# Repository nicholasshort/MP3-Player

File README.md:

# MP3 Player

This is a simple MP3 player designed to be small, lightweight, and long-lasting. The goal is something I can bring on runs, hikes, or long trips that provides 24+ hours of music on a single charge with wired headphones. Firmware is currently in the works, with low level hardware drivers completed.

## Block diagram

## Hardware

- **MCU**: STM32F411CEU6 (Cortex-M4F @ 100 MHz, USB OTG FS)
- **DAC**: TI TAD5242 stereo DAC over I²S, 3.5 mm headphone jack
- **Storage**: microSD card (SPI)
- **Power**: USB-C input, TI BQ24259 Li-ion charger, dual TPS7A20 LDOs for analog/digital rails
- **Controls**: 4 tactile switches (PWR, MENU, PLAY, NEXT), 2 × WS2812B-2020 RGB LEDs
- **PCB**: 4-layer, 50 × 50 mm, KiCad

## Repository layout

- `MP3-Player-PCB/` — KiCad project (schematics, board, libraries)
- `MP3-Player-PCB/Manufacturing/` — Gerbers, BOM, and pick-and-place files for JLCPCB
- `MP3-Player-Firmware/` — STM32CubeIDE project
- `images/` — Photos of the board

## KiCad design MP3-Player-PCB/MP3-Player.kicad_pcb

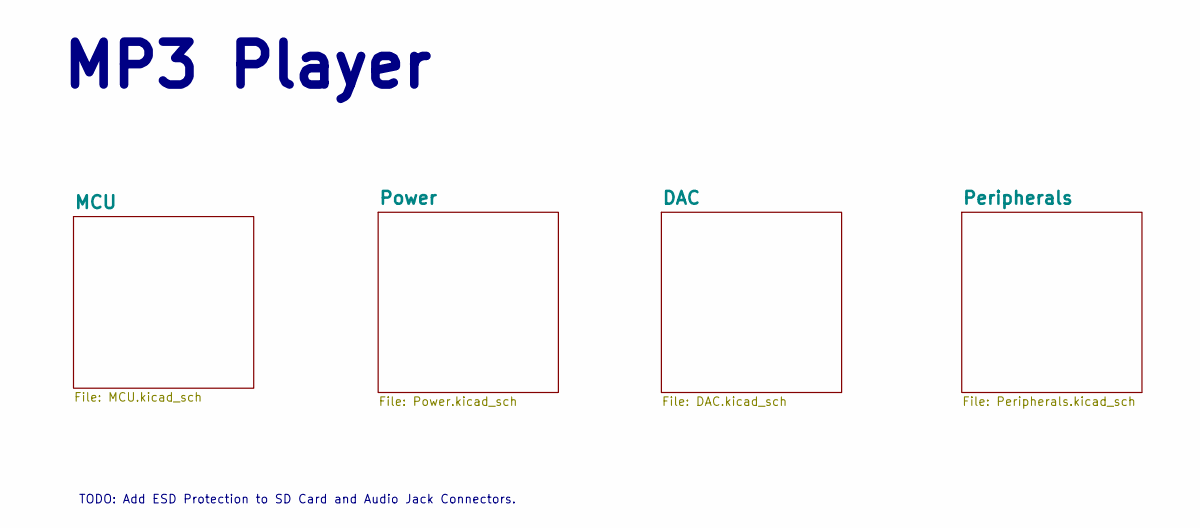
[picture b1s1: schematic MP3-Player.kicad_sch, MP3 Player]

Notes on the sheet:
MP3 Player
TODO: Add ESD Protection to SD Card and Audio Jack Connectors.

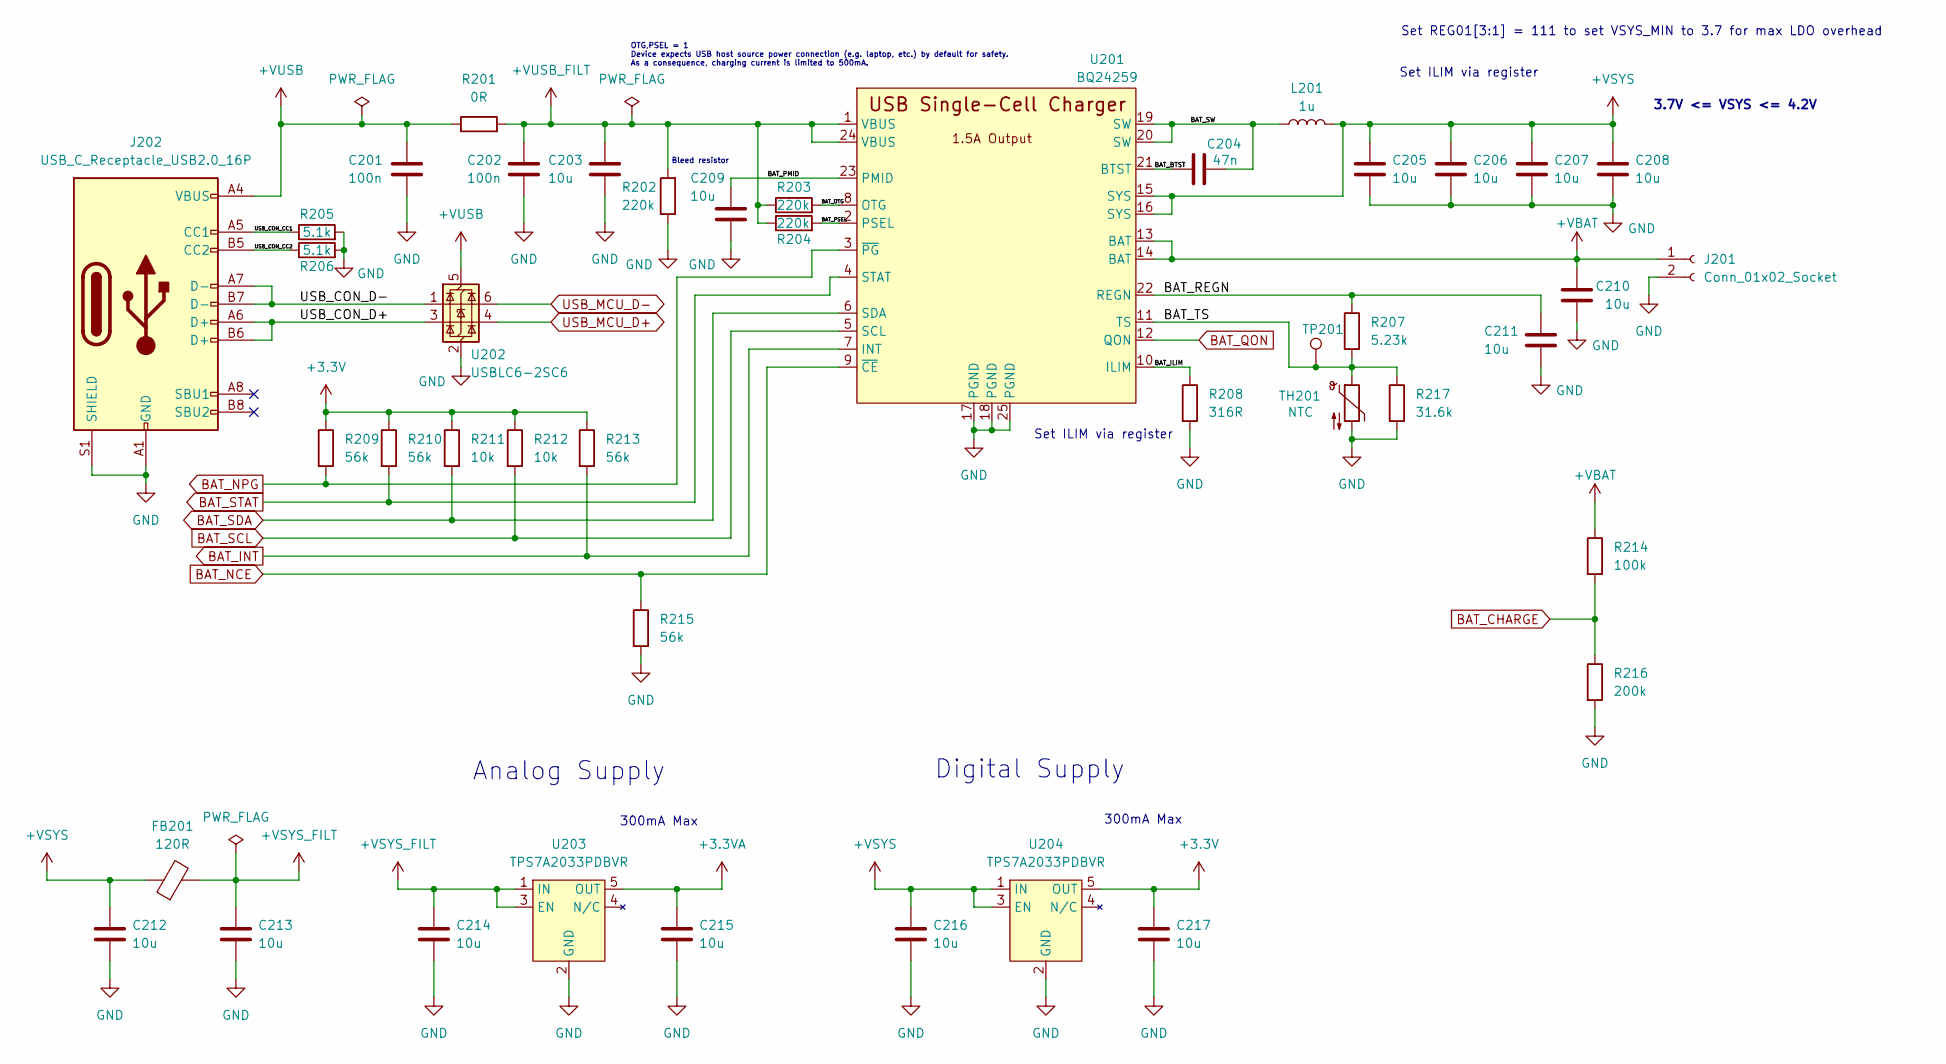
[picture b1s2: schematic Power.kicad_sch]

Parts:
C201, C202: 100n; C_0402_1005Metric; JLCPCB Part # C1525
C203, C209, C211, C212, C213: 10u; C_0603_1608Metric; JLCPCB Part # C19702
C204: 47n; C_0402_1005Metric; JLCPCB Part # C82219
C205, C206, C207, C208, C210, C214, C215, C216, C217: 10u; C_0805_2012Metric; JLCPCB Part # C15850
FB201: 120R; L_0805_2012Metric; JLCPCB Part # C5671
J201: Conn_01x02_Socket; Molex_PicoBlade_53048-0210_1x02_P1.25mm_Horizontal; JLCPCB Part # C505099
J202: USB_C_Receptacle_USB2.0_16P; USB_C_Receptacle_HRO_TYPE-C-31-M-12; JLCPCB Part # C165948
L201: 1u; L_Sunlord_SWPA3015S; JLCPCB Part # C43388
R201: 0R; R_0603_1608Metric; JLCPCB Part # C15402
R202, R203, R204: 220k; R_0402_1005Metric; JLCPCB Part # C25546
R205, R206: 5.1k; R_0402_1005Metric; JLCPCB Part # C25905
R207: 5.23k; R_0402_1005Metric; JLCPCB Part # C25907
R208: 316R; R_0402_1005Metric; JLCPCB Part # C247119
R209, R210, R213, R215: 56k; R_0402_1005Metric; JLCPCB Part # C25796
R211, R212: 10k; R_0402_1005Metric; JLCPCB Part # C25744
R214: 100k; R_0402_1005Metric; JLCPCB Part # C25741
R216: 200k; R_0402_1005Metric; JLCPCB Part # C25764
R217: 31.6k; R_0402_1005Metric; JLCPCB Part # C11463
TH201: NTC; R_0603_1608Metric; JLCPCB Part # C700814
TP201: TestPoint; TestPoint_Pad_1.0x1.0mm
U201: BQ24259; VQFN-24-1EP_4x4mm_P0.5mm_EP2.5x2.5mm; JLCPCB Part # C473366
U202: USBLC6-2SC6; SOT-23-6; JLCPCB Part # C7519
U203, U204: TPS7A2033PDBVR; SOT-23-5; JLCPCB Part # C2862740

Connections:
+3.3V: C217.1, R209.1, R210.1, R211.1, R212.1, R213.1, U204.5 (OUT); also elsewhere on the board
+3.3VA: C215.1, U203.5 (OUT); also elsewhere on the board
+VBAT: C210.1, J201.1, R214.1, U201.13 (BAT), U201.14 (BAT); also elsewhere on the board
+VSYS: C205.1, C206.1, C207.1, C208.1, C212.1, C216.1, FB201.1, L201.2, U201.15 (SYS), U201.16 (SYS), U204.1 (IN), U204.3 (EN); also elsewhere on the board
+VSYS_FILT: C213.1, C214.1, FB201.2, U203.1 (IN), U203.3 (EN)
+VUSB: C201.1, J202.A4 (VBUS), J202.A9 (VBUS), J202.B4 (VBUS), J202.B9 (VBUS), R201.1, U202.5 (VBUS)
+VUSB_FILT: C202.1, C203.1, R201.2, R202.2, R203.1, R204.1, U201.1 (VBUS), U201.24 (VBUS)
/Power/BAT_BTST: C204.1, U201.21 (BTST)
/Power/BAT_ILIM: R208.1, U201.10 (ILIM)
/Power/BAT_OTG: R203.2, U201.8 (OTG)
/Power/BAT_PMID: C209.1, U201.23 (PMID)
/Power/BAT_PSEL: R204.2, U201.2 (PSEL)
/Power/BAT_REGN: C211.1, R207.1, U201.22 (REGN)
/Power/BAT_SW: C204.2, L201.1, U201.19 (SW), U201.20 (SW)
/Power/BAT_TS: R207.2, R217.1, TH201.1, TP201.1, U201.11 (TS)
/Power/USB_CON_CC1: J202.A5 (CC1), R205.1
/Power/USB_CON_CC2: J202.B5 (CC2), R206.1
/Power/USB_CON_D+: J202.A6 (D+), J202.B6 (D+), U202.3 (I/O2)
/Power/USB_CON_D-: J202.A7 (D-), J202.B7 (D-), U202.1 (I/O1)
BAT_CHARGE: R214.2, R216.1; also elsewhere on the board
BAT_INT: R213.2, U201.7 (INT); also elsewhere on the board
BAT_NCE: R215.1, U201.9 (~CE); also elsewhere on the board
BAT_NPG: R209.2, U201.3 (~PG); also elsewhere on the board
BAT_QON: U201.12 (QON); also elsewhere on the board
BAT_SCL: R212.2, U201.5 (SCL); also elsewhere on the board
BAT_SDA: R211.2, U201.6 (SDA); also elsewhere on the board
BAT_STAT: R210.2, U201.4 (STAT); also elsewhere on the board
GND: C201.2, C202.2, C203.2, C205.2, C206.2, C207.2, C208.2, C209.2, C210.2, C211.2, C212.2, C213.2, C214.2, C215.2, C216.2, C217.2, J201.2, J202.A1 (GND), J202.A12 (GND), J202.B1 (GND), J202.B12 (GND), J202.S1 (SHIELD), R202.1, R205.2, R206.2, R208.2, R215.2, R216.2, R217.2, TH201.2, U201.17 (PGND), U201.18 (PGND), U201.25 (PGND), U202.2 (GND), U203.2 (GND), U204.2 (GND); also elsewhere on the board
USB_MCU_D+: U202.4 (I/O2); also elsewhere on the board
USB_MCU_D-: U202.6 (I/O1); also elsewhere on the board

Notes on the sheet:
Analog Supply
Set ILIM via register
Bleed resistor
300mA Max
Digital Supply
OTG,PSEL = 1 Device expects USB host source power connection (e.g. laptop, etc.) by default for safety. As a consequence, charging current is limited to 500mA.
3.7V <= VSYS <= 4.2V
Set REG01[3:1] = 111 to set VSYS_MIN to 3.7 for max LDO overhead

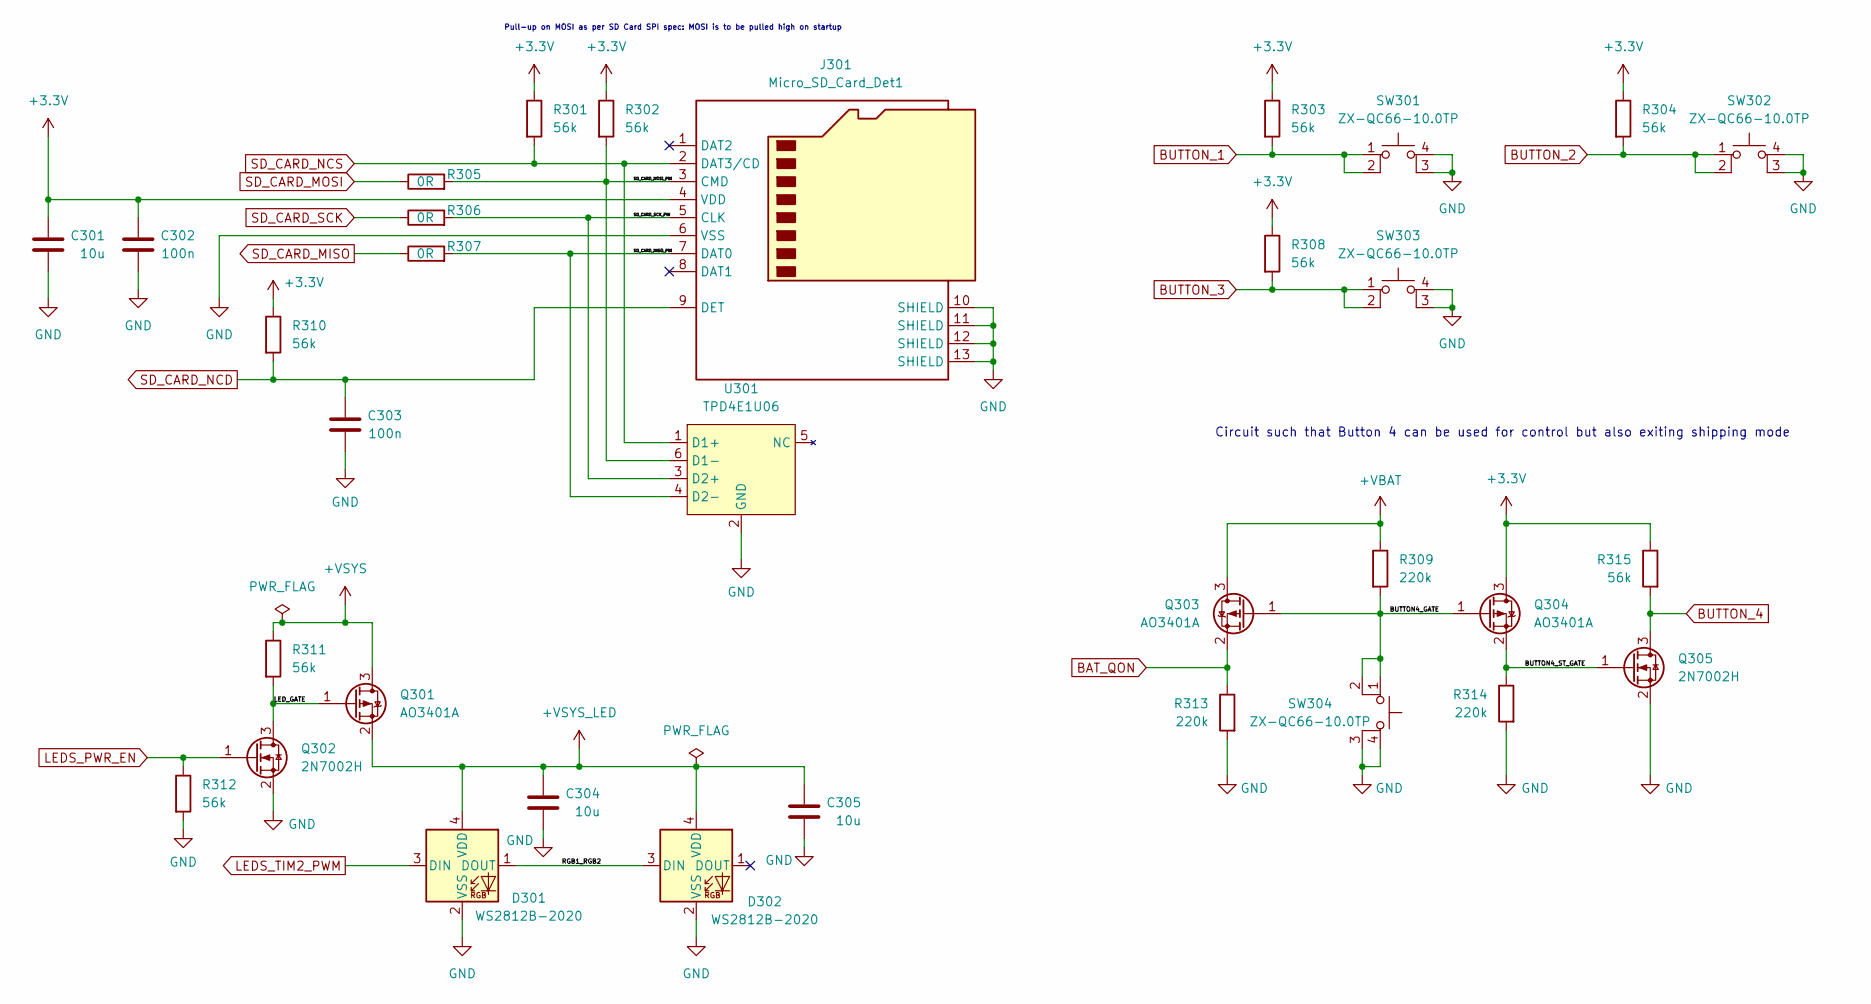
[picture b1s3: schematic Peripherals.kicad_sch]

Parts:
C301, C304, C305: 10u; C_0603_1608Metric; JLCPCB Part # C19702
C302, C303: 100n; C_0402_1005Metric; JLCPCB Part # C1525
D301, D302: WS2812B-2020; LED_WS2812B-2020_PLCC4_2.0x2.0mm; JLCPCB Part # C965555
J301: Micro_SD_Card_Det1; TF-015; JLCPCB Part # C113206
Q301, Q303, Q304: AO3401A; SOT-23; JLCPCB Part # C15127
Q302, Q305: 2N7002H; SOT-23; JLCPCB Part # C3290631
R301, R302, R303, R304, R308, R310, R311, R312, R315: 56k; R_0402_1005Metric; JLCPCB Part # C25796
R305, R306, R307: 0R; R_0402_1005Metric; JLCPCB Part # C17168
R309, R313, R314: 220k; R_0402_1005Metric; JLCPCB Part # C25546
SW301, SW302, SW303, SW304: ZX-QC66-10.0TP; ZX-QC66; JLCPCB Part # C7470162
U301: TPD4E1U06; SOT-23-6; JLCPCB Part # C124691

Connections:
+3.3V: C301.1, C302.1, J301.4 (VDD), Q304.3 (D), R301.1, R302.1, R303.1, R304.1, R308.1, R310.1, R315.1; also elsewhere on the board
+VBAT: Q303.3 (D), R309.1; also elsewhere on the board
+VSYS: Q301.3 (D), R311.1; also elsewhere on the board
+VSYS_LED: C304.1, C305.1, D301.4 (VDD), D302.4 (VDD), Q301.2 (S)
/Peripherals/BUTTON4_GATE: Q303.1 (G), Q304.1 (G), R309.2, SW304.1, SW304.2
/Peripherals/BUTTON4_ST_GATE: Q304.2 (S), Q305.1 (G), R314.1
/Peripherals/LED_GATE: Q301.1 (G), Q302.3 (D), R311.2
/Peripherals/RGB1_RGB2: D301.1 (DOUT), D302.3 (DIN)
/Peripherals/SD_CARD_MISO_PIN: J301.7 (DAT0), R307.2, U301.4 (D2-)
/Peripherals/SD_CARD_MOSI_PIN: J301.3 (CMD), R302.2, R305.2, U301.6 (D1-)
/Peripherals/SD_CARD_SCK_PIN: J301.5 (CLK), R306.2, U301.3 (D2+)
BAT_QON: Q303.2 (S), R313.1; also elsewhere on the board
BUTTON_1: R303.2, SW301.1, SW301.2; also elsewhere on the board
BUTTON_2: R304.2, SW302.1, SW302.2; also elsewhere on the board
BUTTON_3: R308.2, SW303.1, SW303.2; also elsewhere on the board
BUTTON_4: Q305.3 (D), R315.2; also elsewhere on the board
GND: C301.2, C302.2, C303.2, C304.2, C305.2, D301.2 (VSS), D302.2 (VSS), J301.6 (VSS), J301.10 (SHIELD), J301.11 (SHIELD), J301.12 (SHIELD), J301.13 (SHIELD), Q302.2 (S), Q305.2 (S), R312.2, R313.2, R314.2, SW301.3 (K), SW301.4 (A), SW302.3 (K), SW302.4 (A), SW303.3 (K), SW303.4 (A), SW304.3 (K), SW304.4 (A), U301.2 (GND); also elsewhere on the board
LEDS_PWR_EN: Q302.1 (G), R312.1; also elsewhere on the board
LEDS_TIM2_PWM: D301.3 (DIN); also elsewhere on the board
SD_CARD_MISO: R307.1; also elsewhere on the board
SD_CARD_MOSI: R305.1; also elsewhere on the board
SD_CARD_NCD: C303.1, J301.9 (DET), R310.2; also elsewhere on the board
SD_CARD_NCS: J301.2 (DAT3/CD), R301.2, U301.1 (D1+); also elsewhere on the board
SD_CARD_SCK: R306.1; also elsewhere on the board

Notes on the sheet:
Circuit such that Button 4 can be used for control but also exiting shipping mode
Pull-up on MOSI as per SD Card SPI spec: MOSI is to be pulled high on startup

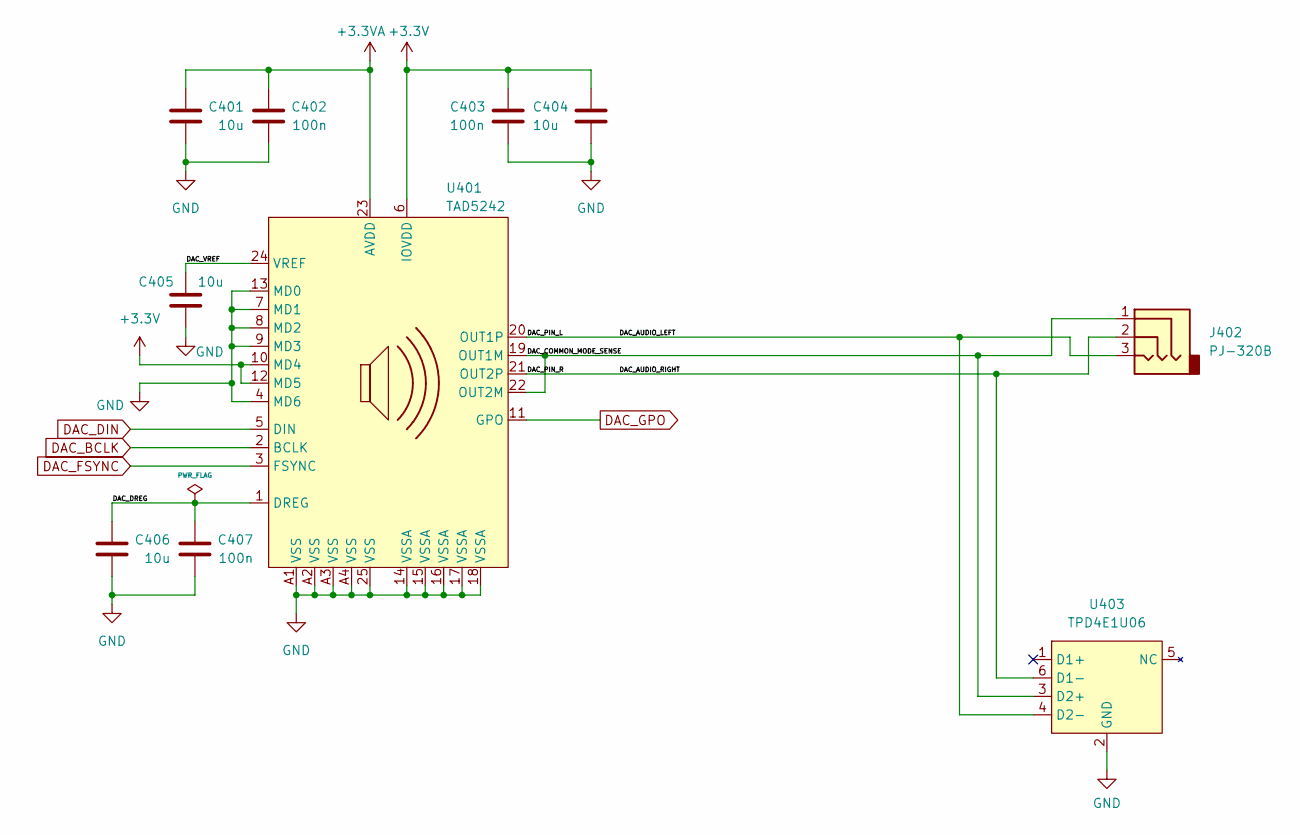
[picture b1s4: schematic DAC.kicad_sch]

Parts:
C401, C404, C405, C406: 10u; C_0603_1608Metric; JLCPCB Part # C19702
C402, C403, C407: 100n; C_0402_1005Metric; JLCPCB Part # C1525
J402: PJ-320B; JLCPCB Part # C18594
U401: TAD5242; JLCPCB Part # C42414591
U403: TPD4E1U06; SOT-23-6; JLCPCB Part # C124691

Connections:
+3.3V: C403.1, C404.1, U401.6 (IOVDD), U401.10 (MD4), U401.12 (MD5); also elsewhere on the board
+3.3VA: C401.1, C402.1, U401.23 (AVDD); also elsewhere on the board
/DAC/DAC_AUDIO_LEFT: J402.3, U401.20 (OUT1P), U403.4 (D2-)
/DAC/DAC_AUDIO_RIGHT: J402.2, U401.21 (OUT2P), U403.6 (D1-)
/DAC/DAC_COMMON_MODE_SENSE: J402.1, U401.19 (OUT1M), U401.22 (OUT2M), U403.3 (D2+)
/DAC/DAC_DREG: C406.1, C407.1, U401.1 (DREG)
/DAC/DAC_VREF: C405.1, U401.24 (VREF)
DAC_BCLK: U401.2 (BCLK); also elsewhere on the board
DAC_DIN: U401.5 (DIN); also elsewhere on the board
DAC_FSYNC: U401.3 (FSYNC); also elsewhere on the board
DAC_GPO: U401.11 (GPO); also elsewhere on the board
GND: C401.2, C402.2, C403.2, C404.2, C405.2, C406.2, C407.2, U401.4 (MD6), U401.7 (MD1), U401.8 (MD2), U401.9 (MD3), U401.13 (MD0), U401.14 (VSSA), U401.15 (VSSA), U401.16 (VSSA), U401.17 (VSSA), U401.18 (VSSA), U401.25 (VSS), U401.A1 (VSS), U401.A2 (VSS), U401.A3 (VSS), U401.A4 (VSS), U403.2 (GND); also elsewhere on the board

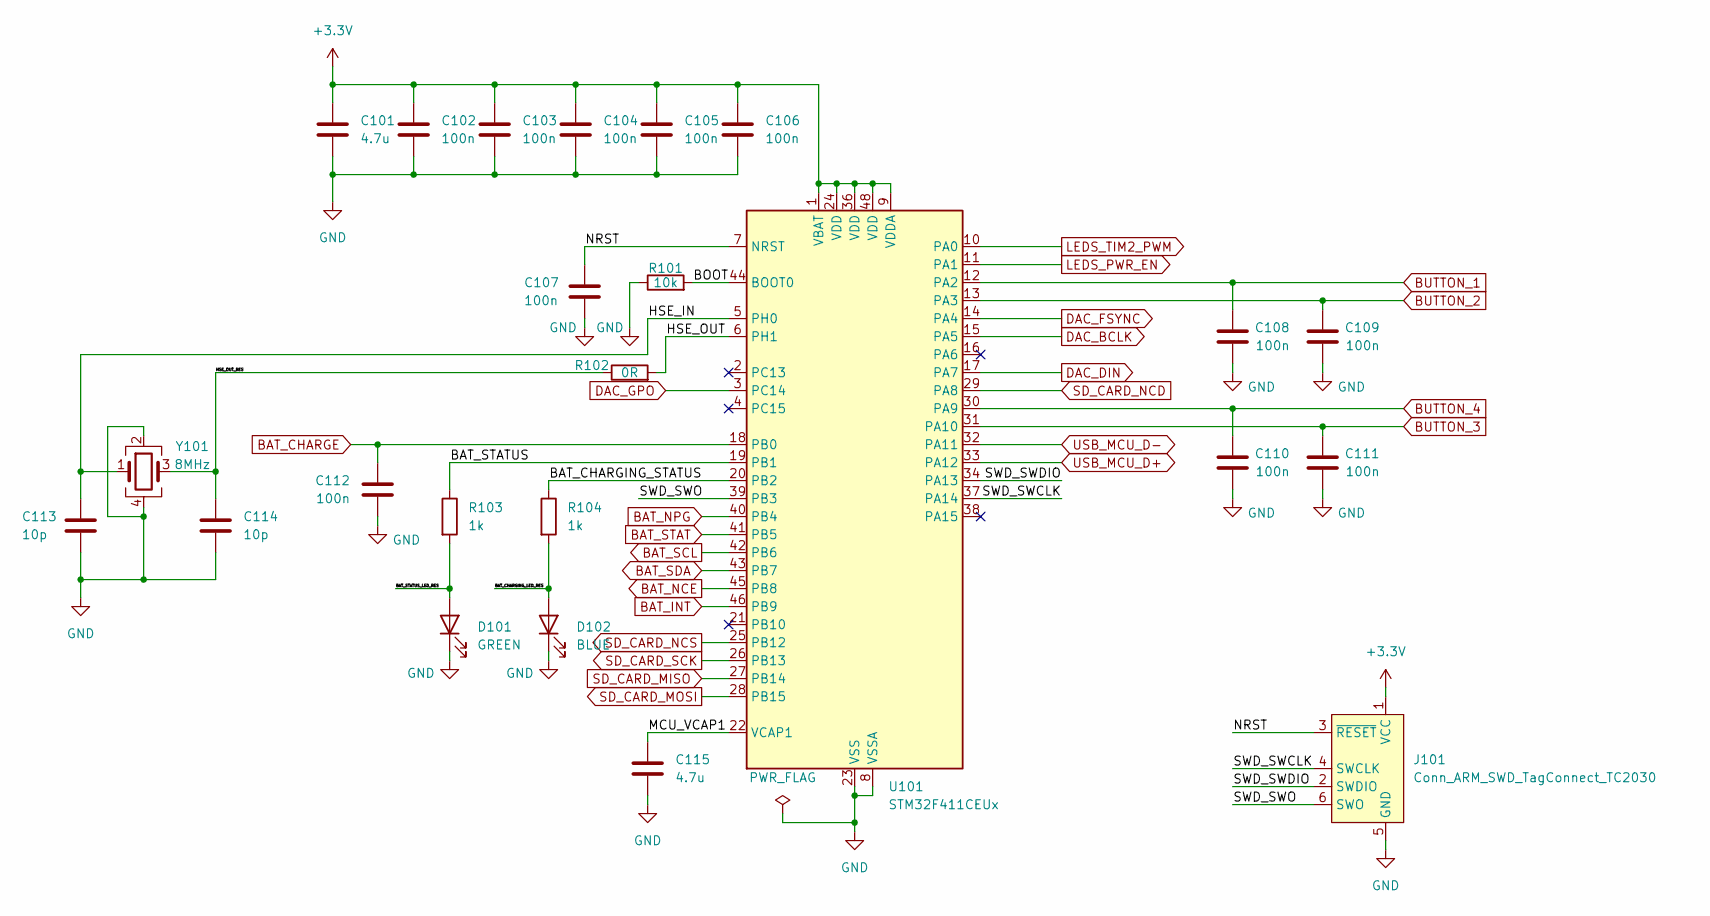
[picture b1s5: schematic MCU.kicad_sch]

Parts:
C101, C115: 4.7u; C_0603_1608Metric; JLCPCB Part # C1705
C102, C103, C104, C105, C106, C107, C108, C109, C110, C111, C112: 100n; C_0402_1005Metric; JLCPCB Part # C1525
C113, C114: 10p; C_0603_1608Metric; JLCPCB Part # C162202
D101: GREEN; LED_0402_1005Metric; JLCPCB Part # C74338
D102: BLUE; LED_0402_1005Metric; JLCPCB Part # C131223
J101: Conn_ARM_SWD_TagConnect_TC2030; Tag-Connect_TC2030-IDC-FP_2x03_P1.27mm_Vertical
R101: 10k; R_0402_1005Metric; JLCPCB Part # C25744
R102: 0R; R_0603_1608Metric; JLCPCB Part # C15402
R103, R104: 1k; R_0402_1005Metric; JLCPCB Part # C11702
U101: STM32F411CEUx; QFN-48-1EP_7x7mm_P0.5mm_EP5.6x5.6mm; JLCPCB Part # C2054095
Y101: 8MHz; Crystal_SMD_3225-4Pin_3.2x2.5mm; JLCPCB Part # C518154

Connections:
+3.3V: C101.1, C102.1, C103.1, C104.1, C105.1, C106.1, J101.1 (VCC), U101.1 (VBAT), U101.9 (VDDA), U101.24 (VDD), U101.36 (VDD), U101.48 (VDD); also elsewhere on the board
/MCU/BAT_CHARGING_LED_RES: D102.2 (A), R104.2
/MCU/BAT_CHARGING_STATUS: R104.1, U101.20 (PB2)
/MCU/BAT_STATUS: R103.1, U101.19 (PB1)
/MCU/BAT_STATUS_LED_RES: D101.2 (A), R103.2
/MCU/BOOT: R101.2, U101.44 (BOOT0)
/MCU/HSE_IN: C113.1, U101.5 (PH0), Y101.1
/MCU/HSE_OUT: R102.2, U101.6 (PH1)
/MCU/HSE_OUT_RES: C114.1, R102.1, Y101.3
/MCU/MCU_VCAP1: C115.1, U101.22 (VCAP1)
/MCU/NRST: C107.1, J101.3 (~RESET), U101.7 (NRST)
/MCU/SWD_SWCLK: J101.4 (SWCLK), U101.37 (PA14)
/MCU/SWD_SWDIO: J101.2 (SWDIO), U101.34 (PA13)
/MCU/SWD_SWO: J101.6 (SWO), U101.39 (PB3)
BAT_CHARGE: C112.1, U101.18 (PB0); also elsewhere on the board
BAT_INT: U101.46 (PB9); also elsewhere on the board
BAT_NCE: U101.45 (PB8); also elsewhere on the board
BAT_NPG: U101.40 (PB4); also elsewhere on the board
BAT_SCL: U101.42 (PB6); also elsewhere on the board
BAT_SDA: U101.43 (PB7); also elsewhere on the board
BAT_STAT: U101.41 (PB5); also elsewhere on the board
BUTTON_1: C108.1, U101.12 (PA2); also elsewhere on the board
BUTTON_2: C109.1, U101.13 (PA3); also elsewhere on the board
BUTTON_3: C111.1, U101.31 (PA10); also elsewhere on the board
BUTTON_4: C110.1, U101.30 (PA9); also elsewhere on the board
DAC_BCLK: U101.15 (PA5); also elsewhere on the board
DAC_DIN: U101.17 (PA7); also elsewhere on the board
DAC_FSYNC: U101.14 (PA4); also elsewhere on the board
DAC_GPO: U101.3 (PC14); also elsewhere on the board
GND: C101.2, C102.2, C103.2, C104.2, C105.2, C106.2, C107.2, C108.2, C109.2, C110.2, C111.2, C112.2, C113.2, C114.2, C115.2, D101.1 (K), D102.1 (K), J101.5 (GND), R101.1, U101.8 (VSSA), U101.23 (VSS), U101.35 (VSS), U101.47 (VSS), U101.49 (VSS), Y101.2, Y101.4; also elsewhere on the board
LEDS_PWR_EN: U101.11 (PA1); also elsewhere on the board
LEDS_TIM2_PWM: U101.10 (PA0); also elsewhere on the board
SD_CARD_MISO: U101.27 (PB14); also elsewhere on the board
SD_CARD_MOSI: U101.28 (PB15); also elsewhere on the board
SD_CARD_NCD: U101.29 (PA8); also elsewhere on the board
SD_CARD_NCS: U101.25 (PB12); also elsewhere on the board
SD_CARD_SCK: U101.26 (PB13); also elsewhere on the board
USB_MCU_D+: U101.33 (PA12); also elsewhere on the board
USB_MCU_D-: U101.32 (PA11); also elsewhere on the board

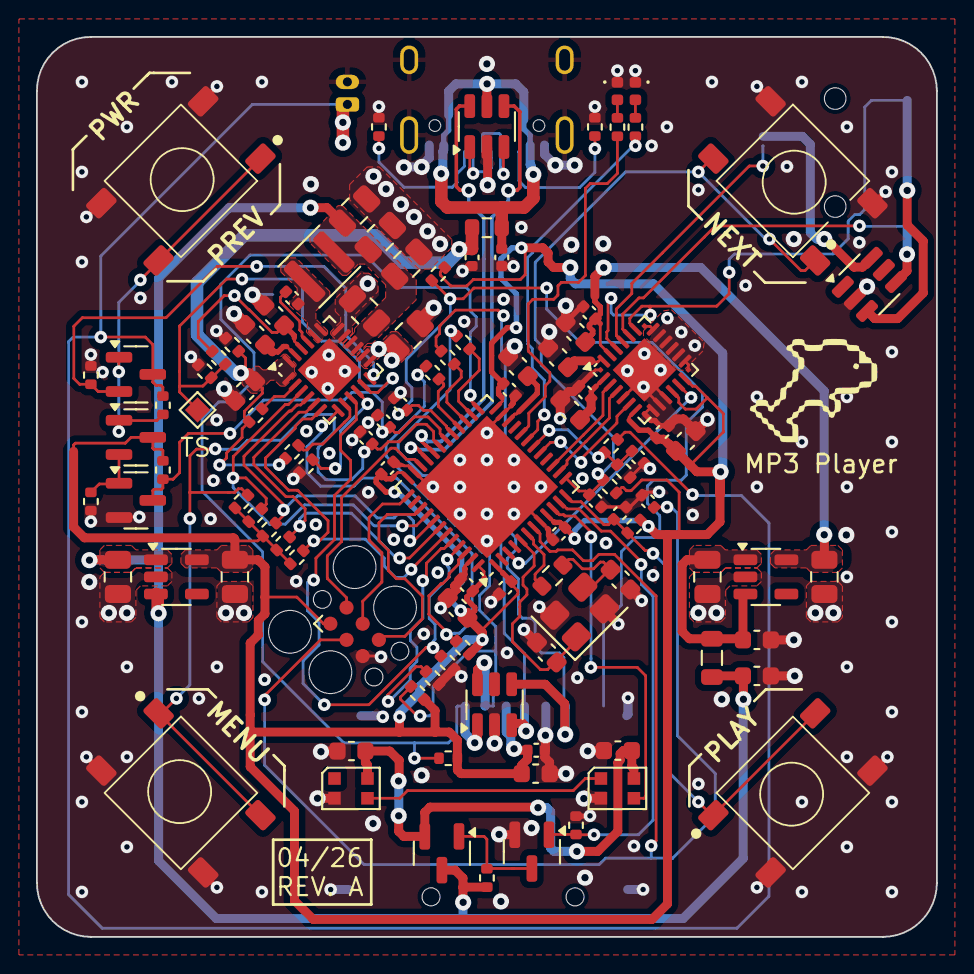
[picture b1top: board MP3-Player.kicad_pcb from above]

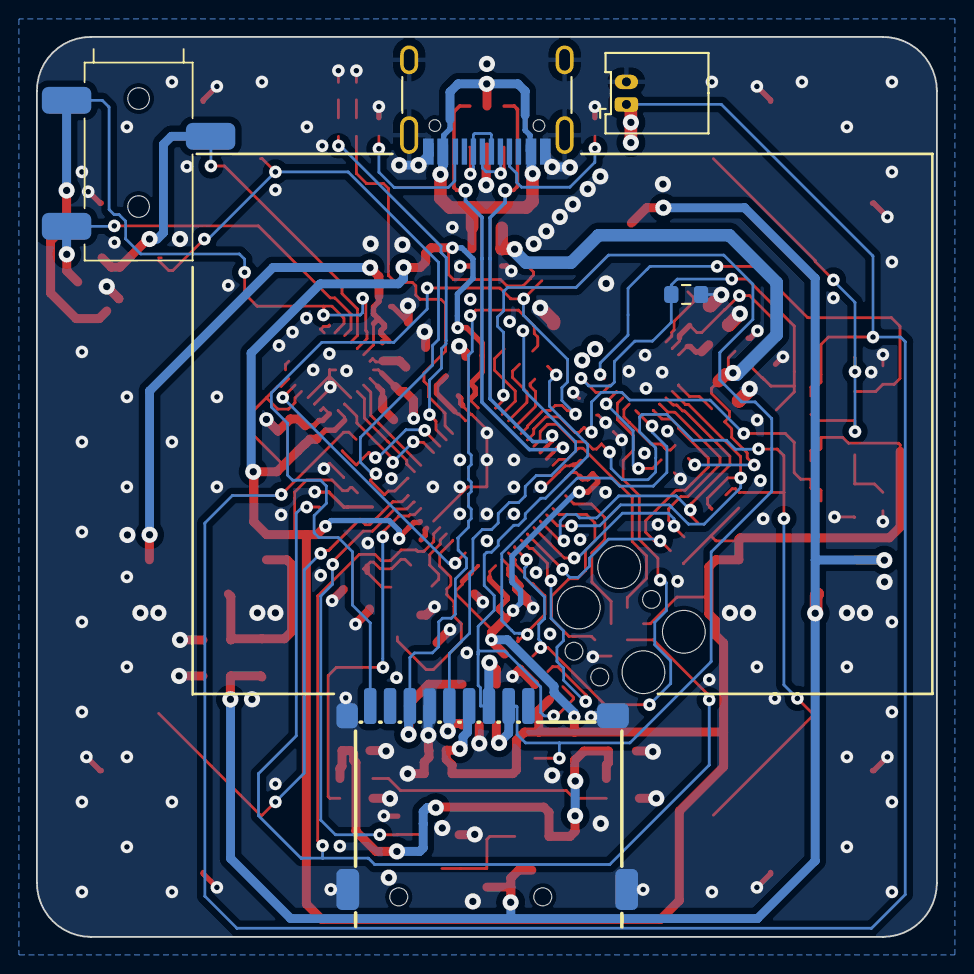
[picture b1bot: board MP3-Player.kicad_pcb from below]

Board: 4 copper layers, 50.0 x 50.0 mm, 111 parts (5 on the bottom side), 71 nets.

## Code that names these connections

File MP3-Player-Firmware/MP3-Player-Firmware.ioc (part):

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Mcu.Name=STM32F411C(C-E)Ux
Mcu.Package=UFQFPN48
Mcu.UserName=STM32F411CEUx
PA0-WKUP.GPIOParameters=GPIO_Label
PA0-WKUP.GPIO_Label=LEDS_PWM
PA0-WKUP.Signal=S_TIM2_CH1_ETR
PA1.GPIOParameters=GPIO_Label
PA1.GPIO_Label=LEDS_PWR_EN
PA1.Signal=GPIO_Output
PA10.GPIOParameters=GPIO_Label
PA10.GPIO_Label=BUTTON_MENU
PA10.Signal=GPIO_Input
PA11.Mode=Device_Only
PA11.Signal=USB_OTG_FS_DM
PA12.Mode=Device_Only
PA12.Signal=USB_OTG_FS_DP
PA13.Mode=Trace_Asynchronous_SW
PA13.Signal=SYS_JTMS-SWDIO
PA14.Mode=Trace_Asynchronous_SW
PA14.Signal=SYS_JTCK-SWCLK
PA2.GPIOParameters=GPIO_Label
PA2.GPIO_Label=BUTTON_PLAY
PA2.Signal=GPIO_Input
PA3.GPIOParameters=GPIO_Label
PA3.GPIO_Label=BUTTON_NEXT
PA3.Signal=GPIO_Input
PA4.Mode=Half_Duplex_Master
PA4.Signal=I2S1_WS
PA5.Mode=Half_Duplex_Master
PA5.Signal=I2S1_CK
PA7.Mode=Half_Duplex_Master
PA7.Signal=I2S1_SD
PA8.GPIOParameters=GPIO_Label
PA8.GPIO_Label=SD_CARD_NCD
PA8.Signal=GPIO_Input
PA9.GPIOParameters=GPIO_Label
PA9.GPIO_Label=BUTTON_PREV_PWR
PA9.Signal=GPIO_Input
PB0.GPIOParameters=GPIO_Label
PB0.GPIO_Label=BAT_CHARGE
PB0.Signal=ADCx_IN8
PB1.GPIOParameters=GPIO_Label
PB1.GPIO_Label=LED_GREEN
PB1.Signal=GPIO_Output
PB12.GPIOParameters=PinState,GPIO_Label
PB12.GPIO_Label=SD_CARD_NCS
PB12.PinState=GPIO_PIN_SET
PB12.Signal=GPIO_Output
PB13.GPIOParameters=GPIO_Label
PB13.GPIO_Label=SD_CARD_SCK
PB13.Mode=Full_Duplex_Master
PB13.Signal=SPI2_SCK
PB14.GPIOParameters=GPIO_Label
PB14.GPIO_Label=SD_CARD_MISO
PB14.Mode=Full_Duplex_Master
PB14.Signal=SPI2_MISO
PB15.GPIOParameters=GPIO_Label
PB15.GPIO_Label=SD_CARD_MOSI
PB15.Mode=Full_Duplex_Master
PB15.Signal=SPI2_MOSI
PB2.GPIOParameters=GPIO_Label
PB2.GPIO_Label=LED_BLUE
PB2.Signal=GPIO_Output
PB3.Mode=Trace_Asynchronous_SW
PB3.Signal=SYS_JTDO-SWO
PB4.GPIOParameters=GPIO_Label
PB4.GPIO_Label=BAT_NPG
PB4.Signal=GPIO_Input
PB5.GPIOParameters=GPIO_Label
PB5.GPIO_Label=BAT_STAT
PB5.Signal=GPIO_Input
PB6.GPIOParameters=GPIO_Label
PB6.GPIO_Label=BAT_SCL
PB6.Mode=I2C
PB6.Signal=I2C1_SCL
PB7.GPIOParameters=GPIO_Label
PB7.GPIO_Label=BAT_SDA
PB7.Mode=I2C
PB7.Signal=I2C1_SDA
PB8.GPIOParameters=GPIO_Label
PB8.GPIO_Label=BAT_NCE
PB8.Signal=GPIO_Output
PB9.GPIOParameters=GPIO_Label
PB9.GPIO_Label=BAT_INT
PB9.Signal=GPIO_Input
PC14-OSC32_IN.GPIOParameters=GPIO_Label
PC14-OSC32_IN.GPIO_Label=DAC_GPO
PC14-OSC32_IN.Signal=GPIO_Input
PH0\ -\ OSC_IN.Mode=HSE-External-Oscillator
PH0\ -\ OSC_IN.Signal=RCC_OSC_IN
PH1\ -\ OSC_OUT.Mode=HSE-External-Oscillator
PH1\ -\ OSC_OUT.Signal=RCC_OSC_OUT
RCC.HSE_VALUE=8000000
RCC.SYSCLKFreq_VALUE=96000000.00000001
RCC.SYSCLKSource=RCC_SYSCLKSOURCE_PLLCLK
board=custom

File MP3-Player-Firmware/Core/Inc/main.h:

/* USER CODE BEGIN Header */
/**
  ******************************************************************************
  * @file           : main.h
  * @brief          : Header for main.c file.
  *                   This file contains the common defines of the application.
  ******************************************************************************
  * @attention
  *
  * Copyright (c) 2026 STMicroelectronics.
  * All rights reserved.
  *
  * This software is licensed under terms that can be found in the LICENSE file
  * in the root directory of this software component.
  * If no LICENSE file comes with this software, it is provided AS-IS.
  *
  ******************************************************************************
  */
/* USER CODE END Header */

/* Define to prevent recursive inclusion -------------------------------------*/
#ifndef __MAIN_H
#define __MAIN_H

#ifdef __cplusplus
extern "C" {
#endif

/* Includes ------------------------------------------------------------------*/
#include "stm32f4xx_hal.h"

/* Private includes ----------------------------------------------------------*/
/* USER CODE BEGIN Includes */

/* USER CODE END Includes */

/* Exported types ------------------------------------------------------------*/
/* USER CODE BEGIN ET */

/* USER CODE END ET */

/* Exported constants --------------------------------------------------------*/
/* USER CODE BEGIN EC */

/* USER CODE END EC */

/* Exported macro ------------------------------------------------------------*/
/* USER CODE BEGIN EM */

/* USER CODE END EM */

/* Exported functions prototypes ---------------------------------------------*/
void Error_Handler(void);

/* USER CODE BEGIN EFP */

/* USER CODE END EFP */

/* Private defines -----------------------------------------------------------*/
#define DAC_GPO_Pin GPIO_PIN_14
#define DAC_GPO_GPIO_Port GPIOC
#define LEDS_PWM_Pin GPIO_PIN_0
#define LEDS_PWM_GPIO_Port GPIOA
#define LEDS_PWR_EN_Pin GPIO_PIN_1
#define LEDS_PWR_EN_GPIO_Port GPIOA
#define BUTTON_PLAY_Pin GPIO_PIN_2
#define BUTTON_PLAY_GPIO_Port GPIOA
#define BUTTON_NEXT_Pin GPIO_PIN_3
#define BUTTON_NEXT_GPIO_Port GPIOA
#define BAT_CHARGE_Pin GPIO_PIN_0
#define BAT_CHARGE_GPIO_Port GPIOB
#define LED_GREEN_Pin GPIO_PIN_1
#define LED_GREEN_GPIO_Port GPIOB
#define LED_BLUE_Pin GPIO_PIN_2
#define LED_BLUE_GPIO_Port GPIOB
#define SD_CARD_NCS_Pin GPIO_PIN_12
#define SD_CARD_NCS_GPIO_Port GPIOB
#define SD_CARD_SCK_Pin GPIO_PIN_13
#define SD_CARD_SCK_GPIO_Port GPIOB
#define SD_CARD_MISO_Pin GPIO_PIN_14
#define SD_CARD_MISO_GPIO_Port GPIOB
#define SD_CARD_MOSI_Pin GPIO_PIN_15
#define SD_CARD_MOSI_GPIO_Port GPIOB
#define SD_CARD_NCD_Pin GPIO_PIN_8
#define SD_CARD_NCD_GPIO_Port GPIOA
#define BUTTON_PREV_PWR_Pin GPIO_PIN_9
#define BUTTON_PREV_PWR_GPIO_Port GPIOA
#define BUTTON_MENU_Pin GPIO_PIN_10
#define BUTTON_MENU_GPIO_Port GPIOA
#define BAT_NPG_Pin GPIO_PIN_4
#define BAT_NPG_GPIO_Port GPIOB
#define BAT_STAT_Pin GPIO_PIN_5
#define BAT_STAT_GPIO_Port GPIOB
#define BAT_SCL_Pin GPIO_PIN_6
#define BAT_SCL_GPIO_Port GPIOB
#define BAT_SDA_Pin GPIO_PIN_7
#define BAT_SDA_GPIO_Port GPIOB
#define BAT_NCE_Pin GPIO_PIN_8
#define BAT_NCE_GPIO_Port GPIOB
#define BAT_INT_Pin GPIO_PIN_9
#define BAT_INT_GPIO_Port GPIOB

/* USER CODE BEGIN Private defines */

/* USER CODE END Private defines */

#ifdef __cplusplus
}
#endif

#endif /* __MAIN_H */

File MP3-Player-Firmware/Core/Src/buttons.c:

#include "buttons.h"

#include "main.h"
#include "stm32f4xx_hal.h"

typedef struct
{
    GPIO_TypeDef *port;
    uint16_t pin;
    bool pressed;
} button_t;

static button_t buttons[BUTTON_COUNT] =
{
    [BUTTON_1] =
    {
        .port = BUTTON_1_GPIO_Port,
        .pin = BUTTON_1_Pin,
        .pressed = false,
    },
    [BUTTON_2] =
    {
        .port = BUTTON_2_GPIO_Port,
        .pin = BUTTON_2_Pin,
        .pressed = false,
    },
    [BUTTON_3] =
    {
        .port = BUTTON_3_GPIO_Port,
        .pin = BUTTON_3_Pin,
        .pressed = false,
    },
    [BUTTON_4] =
    {
        .port = BUTTON_4_GPIO_Port,
        .pin = BUTTON_4_Pin,
        .pressed = false,
    },
};

static bool button_read_pressed(GPIO_TypeDef *port, uint16_t pin)
{
    /*
     * Hardware has external pull-ups:
     * released = high
     * pressed  = low
     */
    return HAL_GPIO_ReadPin(port, pin) == GPIO_PIN_RESET;
}

void buttons_init(void)
{
    buttons_poll();
}

void buttons_poll(void)
{
    for (uint32_t i = 0; i < BUTTON_COUNT; i++)
    {
        buttons[i].pressed = button_read_pressed(buttons[i].port, buttons[i].pin);
    }
}

bool buttons_is_pressed(button_id_t button)
{
    if (button >= BUTTON_COUNT)
    {
        return false;
    }

    return buttons[button].pressed;
}

button_state_t buttons_get_state(void)
{
    button_state_t state =
    {
        .button_1 = buttons[BUTTON_1].pressed,
        .button_2 = buttons[BUTTON_2].pressed,
        .button_3 = buttons[BUTTON_3].pressed,
        .button_4 = buttons[BUTTON_4].pressed,
    };

    return state;
}

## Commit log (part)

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2025-07-28 Created USB Charger IC schematic symbol
2025-07-29 Added all schematic symbols. Time to start wiring up!
2025-07-29 Finished cookie-cutter mcu routing
2025-08-01 Up to date
2025-08-14 Started power schematic
2025-08-17 Adding i2c connections to charger ic as well as ntc safety logic
2025-08-17 Added charger IC schematic circuitry
2025-08-17 Removing empty directory
2025-11-14 Added new LDO (TPS7A20) schematic symbol and wired it up on power page for both analog and digital supplies
2025-11-14 Completed DAC circuitry
2025-11-14 Beginning of the pinout in cubemx
2025-11-16 Finished SD card connections with MCU
2025-11-16 Added addressable LED circuitry
2025-11-16 Added button circuitry
2025-11-16 Added esd protection to audiojack and sd card. Also added jack detection on audiojack
2025-11-17 Added adc pin and voltage divider to read battery voltage. Also added charging status leds, and assigned some footprints
2025-11-18 Assigned all footprints
2025-11-22 Fixed all ERC errors
2025-11-22 Imported board stackup
2025-11-24 Fixed all import change from schematic errors and warnings
2025-11-24 Added 3D models for all components
2025-12-04 Near completion of layout
2025-12-08 Finished rough layout. New Audio jack still required
2025-12-13 Final Layout
2025-12-13 Adding GND vias
2026-01-25 Much better initial layout
2026-01-26 Cleaned up layout yet again for proper routing. Started preliminary routing
2026-02-02 Routing more mcu signals
2026-02-05 Continuing routing
2026-02-25 Finished SD card routing
2026-03-08 Finished RGB LED routing
2026-03-09 Completed much of the USB-C charging IC power routing
2026-03-10 Routed button gpio signals
2026-03-12 Finished USB power routing
2026-03-12 Changing JST connector footprint to fit next to usb
2026-03-13 Routed VBAT power trace in 3rd layer
2026-03-21 Finished signal routing for charger ic
2026-03-22 Routed out shipping mode exit logic circuitry
2026-03-23 Finished routing more miscellaneous signals
2026-03-27 Replaced THT buttons with SMT
2026-03-30 Finished Audio Jack routing
2026-04-17 Finished routinggit status! DRC needed
2026-04-20 Fixed all DRC errors
2026-04-21 Added stitching vias
2026-04-24 Assigning JLCPCB part #'s
2026-04-24 Added 5.25k resistor to thermistor divider network as per BQ24259 datasheet
2026-04-25 Replaced JST connector with picoblade to match purchased battery
2026-04-26 Fixing common mode sense node on audio output
2026-04-27 Added JLCPCB part numbers for remaining parts
2026-04-27 Ordered MP3 Playergit status! Finally :)
2026-05-03 Updating gitignore to include csv files
2026-05-03 Adding component placement and BOM which were previously ignored by gitignore
2026-05-12 Added README and Licenses
2026-05-12 Rotating images such that they work with README
2026-05-12 Editing README
2026-05-15 Fixing io on mx
2026-05-15 Tested DAC and GPIO LEDs!
2026-05-19 Added button test code
2026-05-21 Removing build directory from repo
2026-05-22 Testing USB Charger IC. Looks good
2026-05-22 Working SD card test
2026-05-23 Adding .vscode to gitignore
2026-05-23 Working BQ24259 driver init function
2026-05-23 Added reading status and fault register functions
2026-05-23 Finished BQ24259 driver
2026-05-23 Tested and working BQ24259 driver!
2026-05-24 Added button driver
2026-05-24 Added button testing code
2026-05-25 Wrote and tested status led driver
2026-06-02 Added CubeMX timer PWM stock code
2026-06-05 Working ws2812b driver :) Fantastic stuff
2026-06-05 Fixing LEFT and RIGHT RGB LED orientation in driver
2026-06-07 Working CMD0 packet sent to sd card
2026-06-07 Working CMD8 sent and R7 expected response
2026-06-12 Working complete card initialization testing
2026-06-15 Working read_block function
2026-06-16 Tested read_blocks code
2026-06-16 Working read_blocks functions
2026-06-16 Adding initialization status helper to SD card spi
2026-06-16 Working FatFs integration
2026-06-17 First crack at tad5242 driver with test code
2026-06-18 Working sinusoid playback
2026-06-18 Cleaning up driver
2026-06-18 Working audio playback/streaming! Some pops need to be worked out
2026-06-18 Enabling TIM5 to act as free-running profiler timer
2026-06-19 Tracking down poor audio bug
2026-06-19 Working on CMD18 multi block transfers to speed up SD card reads
2026-06-23 Added contiguous block reads to read_blocks function
2026-06-23 Broken 1kHz sin wave
2026-06-23 Fixed I2S frame format bug. Audio now working again
2026-06-24 No more overruns! Perfect playback. Changed added read_buffer_fast to get around read_buffer's byte_by_byte transmission
2026-06-25 Add Helix MP3 decoder
2026-06-25 Working mp3 audio playback. Completely AI written
2026-06-26 Remove helix-mp3 submodule
2026-06-26 Remove empty .gitmodules
2026-06-26 Added forked copy of helix-mp3
2026-06-29 Updating README
2026-06-29 Adding new photo and block diagram to README
2026-06-30 Adding ring buffer implementation and common directory
2026-06-30 Added reading memory blocks from ring buffer
